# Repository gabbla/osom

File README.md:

# **Open speedomenter** **WIP**

**OSOM** (read as _ˈôsəm_) is the acronym of Open Speedometer.

## Architecture
The new architecture is the following:

Clinet <==BLE==> Master <==2.4GHz==> Slave

where:
- Master: CC2541 <==UART==> PIC <==SPI==> nRF24L01+
- Slave:  PIC <==SPI==> nRF24L01+

The client is a device that must be compatible with BLE (Bluetooth 4.x).

The CC2541 (aka NP, aka Network Processor) will run a standard firmware that is in charge of providing a bluetooth connection to the PIC.

Master and Slave will exchange messages over a custom, light-weight, protocol.

## Specifications

- Microcontroller: PIC32MX274F256D @72MHz (TODO verify)
- Communication:
	- Bluetooth (master only): HM10 Bluetooth 4.2 Low Energy
	- Wireless: nRF24L01+ @2.4GHz
- Power: 
	- LiPo 1s Battery, 1200/2000 mAh (not choosen yet)
	- 5V provided by micro USB, 500 mA MAX
- Sensor: custom made 650nm modulated laser sensor 
- Laser source: Red diode laser, 650nm @5mW

## PIC PIN assignment

### Bluetooth (master only)

PIN|I/O|PPS|Function|Note
--|--|--|--|--|
6|IN|RPB2|U1RX|PIC <== NP
7|OUT|RPB3|U1TX|PIC ==> NP

### nRF24L01+

PIN|I/O|PPS|Function|Note
--|--|--|--|--|
21|IN|RPB10|INT1|Interrupt generated by nRF24L01+
22|OUT|RPB11|SDO2|
23|OUT|-|CS|RB12
24|IN|RPB13|SDI2|
25|OUT|-|CE|RB14
26|OUT|RPB15|SCK2|

### Debug

PIN|I/O|PPS|Function|Note
--|--|--|--|--|
4|OUT|RPB0|U2TX|PIC ==> PC
5|IN|RPB1|U2RX|PIC <== PC

USB will be available too, with at least a _comunication device class_ (CDC) enumeration. 

### Sensing

PIN|I/O|PPS|Function|Note
--|--|--|--|--|
16|IN|-|INT0|Left IN Interrupt
11|IN|RPB4|INT4|Right IN Interrupt

### Battery Charger

New PIC analisys required

### LEDs

Analisys required. 

**Note**
1. Master only: an extra LED from CC2541 indicates the BT connection status.
2. From the battery charger an extra LED indicates che charging status.

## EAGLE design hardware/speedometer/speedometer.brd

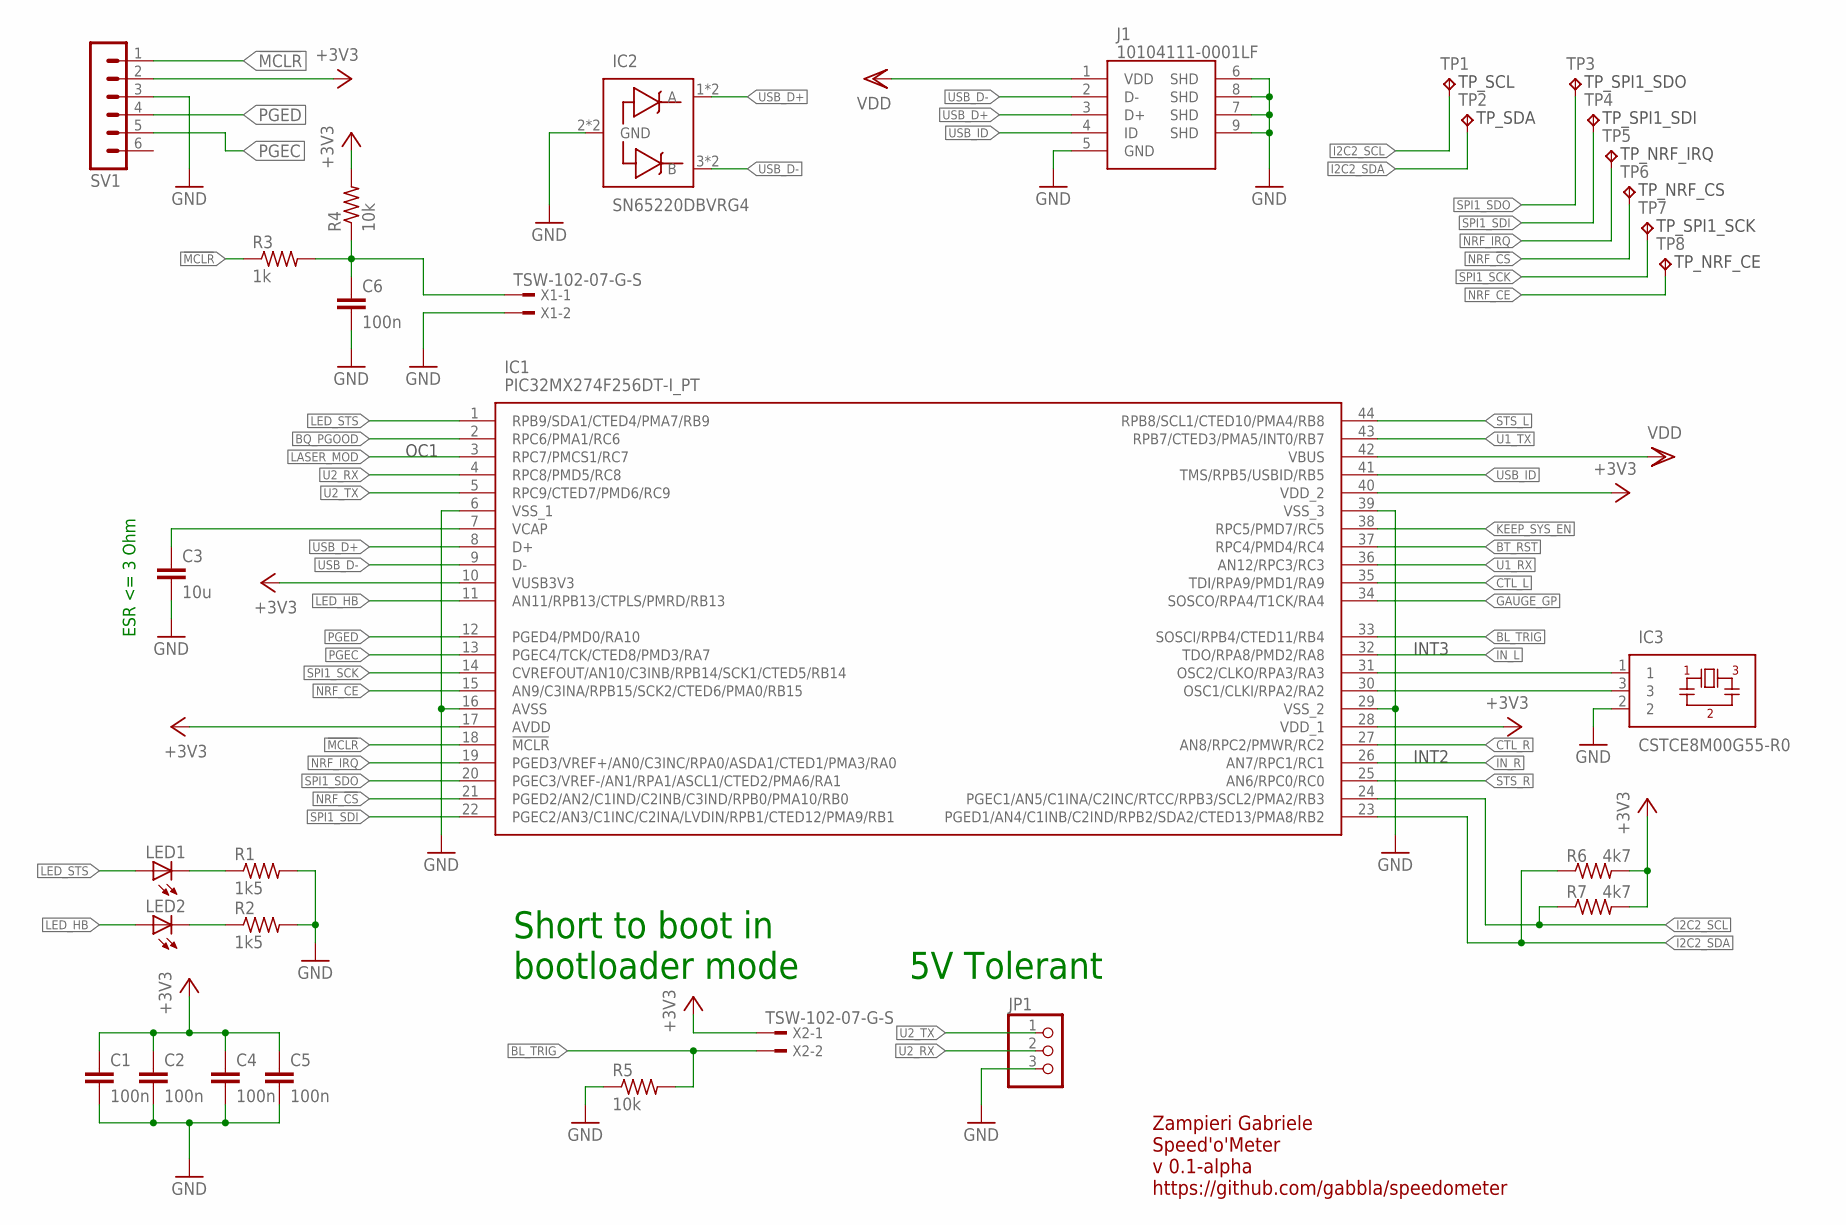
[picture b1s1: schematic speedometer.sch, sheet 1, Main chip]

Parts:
C1, C2, C4, C5, C6: 100n; C0603K
C3: 10u; C0805K
IC1: PIC32MX274F256DT-I_PT; QFP80P1200X1200X120-44N
IC2: SN65220DBVRG4; SOT95P280X145-6N
IC3: CSTCE8M00G55-R0; CSTCE_G
J1: 10104111-0001LF; MICRO_USB_A/B_TYPE_RECEPTACLE
JP1: PINHD-1X3; 1X03
LED1: LED3MM
LED2: LEDCHIPLED_0805; CHIPLED_0805
R1, R2: 1k5; R0603
R3: 1k; R0603
R4, R5: 10k; R0603
R6, R7: 4k7; R0603
SV1: MA06-1
TP1, TP2, TP3, TP4, TP5, TP6, TP7, TP8: TPB1,27; B1,27
X1, X2: TSW-102-07-G-S; TSW-102-XX-G-S

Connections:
!MCLR: IC1.18 (!MCLR), R3.1, SV1.1
+3V3: C1.1, C2.1, C4.1, C5.1, IC1.10 (VUSB3V3), IC1.17 (AVDD), IC1.28 (VDD_1), IC1.40 (VDD_2), R4.2, R6.2, R7.2, SV1.2, X2.1; also elsewhere on the board
BL_TRIG: IC1.33 (SOSCI/RPB4/CTED11/RB4), R5.2, X2.2
BQ_PGOOD: IC1.2 (RPC6/PMA1/RC6); also elsewhere on the board
BT_RST: IC1.37 (RPC4/PMD4/RC4); also elsewhere on the board
CTL_L: IC1.35 (TDI/RPA9/PMD1/RA9); also elsewhere on the board
CTL_R: IC1.27 (AN8/RPC2/PMWR/RC2); also elsewhere on the board
GAUGE_GP: IC1.34 (SOSCO/RPA4/T1CK/RA4); also elsewhere on the board
GND: C1.2, C2.2, C3.2, C4.2, C5.2, C6.2, IC1.6 (VSS_1), IC1.16 (AVSS), IC1.29 (VSS_2), IC1.39 (VSS_3), IC2.2 (GND), IC2.5 (GND), IC3.2, J1.5 (GND), J1.6 (SHD), J1.7 (SHD), J1.8 (SHD), J1.9 (SHD), JP1.3, R1.2, R2.2, R5.1, SV1.3, X1.2; also elsewhere on the board
I2C2_SCL: IC1.24 (PGEC1/AN5/C1INA/C2INC/RTCC/RPB3/SCL2/PM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), R7.1, TP1.TP; also elsewhere on the board
I2C2_SDA: IC1.23 (PGED1/AN4/C1INB/C2IND/RPB2/SDA2/CTED13/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), R6.1, TP2.TP; also elsewhere on the board
IN_L: IC1.32 (TDO/RPA8/PMD2/RA8); also elsewhere on the board
IN_R: IC1.26 (AN7/RPC1/RC1); also elsewhere on the board
KEEP_SYS_EN: IC1.38 (RPC5/PMD7/RC5); also elsewhere on the board
LASER_MOD: IC1.3 (RPC7/PMCS1/RC7); also elsewhere on the board
LED_HB: IC1.11 (AN11/RPB13/CTPLS/PMRD/RB13), LED2.A
LED_STS: IC1.1 (RPB9/SDA1/CTED4/PMA7/RB9), LED1.A
unnamed: LED1.K (C), R1.1
unnamed: IC1.31 (OSC2/CLKO/RPA3/RA3), IC3.1
unnamed: IC1.30 (OSC1/CLKI/RPA2/RA2), IC3.3
unnamed: C3.1, IC1.7 (VCAP)
unnamed: LED2.C, R2.1
unnamed: C6.1, R3.2, R4.1, X1.1
NRF_!CS: IC1.21 (PGED2/AN2/C1IND/C2INB/C3IND/RPB0/PMA10/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), TP6.TP; also elsewhere on the board
NRF_CE: IC1.15 (AN9/C3INA/RPB15/SCK2/CTED6/PMA0/RB15), TP8.TP; also elsewhere on the board
NRF_IRQ: IC1.19 (PGED3/VREF+/AN0/C3INC/RPA0/ASDA1/CTED1/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), TP5.TP; also elsewhere on the board
PGEC: IC1.13 (PGEC4/TCK/CTED8/PMD3/RA7), SV1.5
PGED: IC1.12 (PGED4/PMD0/RA10), SV1.4
SPI1_SCK: IC1.14 (CVREFOUT/AN10/C3INB/RPB14/SCK1/CTED5/RB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), TP7.TP; also elsewhere on the board
SPI1_SDI: IC1.22 (PGEC2/AN3/C1INC/C2INA/LVDIN/RPB1/CTED12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), TP4.TP; also elsewhere on the board
SPI1_SDO: IC1.20 (PGEC3/VREF-/AN1/RPA1/ASCL1/CTED2/PMA6/R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), TP3.TP; also elsewhere on the board
STS_L: IC1.44 (RPB8/SCL1/CTED10/PMA4/RB8); also elsewhere on the board
STS_R: IC1.25 (AN6/RPC0/RC0); also elsewhere on the board
U1_RX: IC1.36 (AN12/RPC3/RC3); also elsewhere on the board
U1_TX: IC1.43 (RPB7/CTED3/PMA5/INT0/RB7); also elsewhere on the board
U2_RX: IC1.4 (RPC8/PMD5/RC8), JP1.2
U2_TX: IC1.5 (RPC9/CTED7/PMD6/RC9), JP1.1
USB_D+: IC1.8 (D+), IC2.1 (A), IC2.6 (A), J1.3 (D+)
USB_D-: IC1.9 (D-), IC2.3 (B), IC2.4 (B), J1.2 (D-)
USB_ID: IC1.41 (TMS/RPB5/USBID/RB5), J1.4 (ID)
VDD: IC1.42 (VBUS), J1.1 (VDD); also elsewhere on the board

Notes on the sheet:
Zampieri Gabriele Speed'o'Meter v 0.1-alpha https://github.com/gabbla/speedometer
ESR <= 3 Ohm
5V Tolerant
Short to boot in bootloader mode
OC1
INT2
INT3

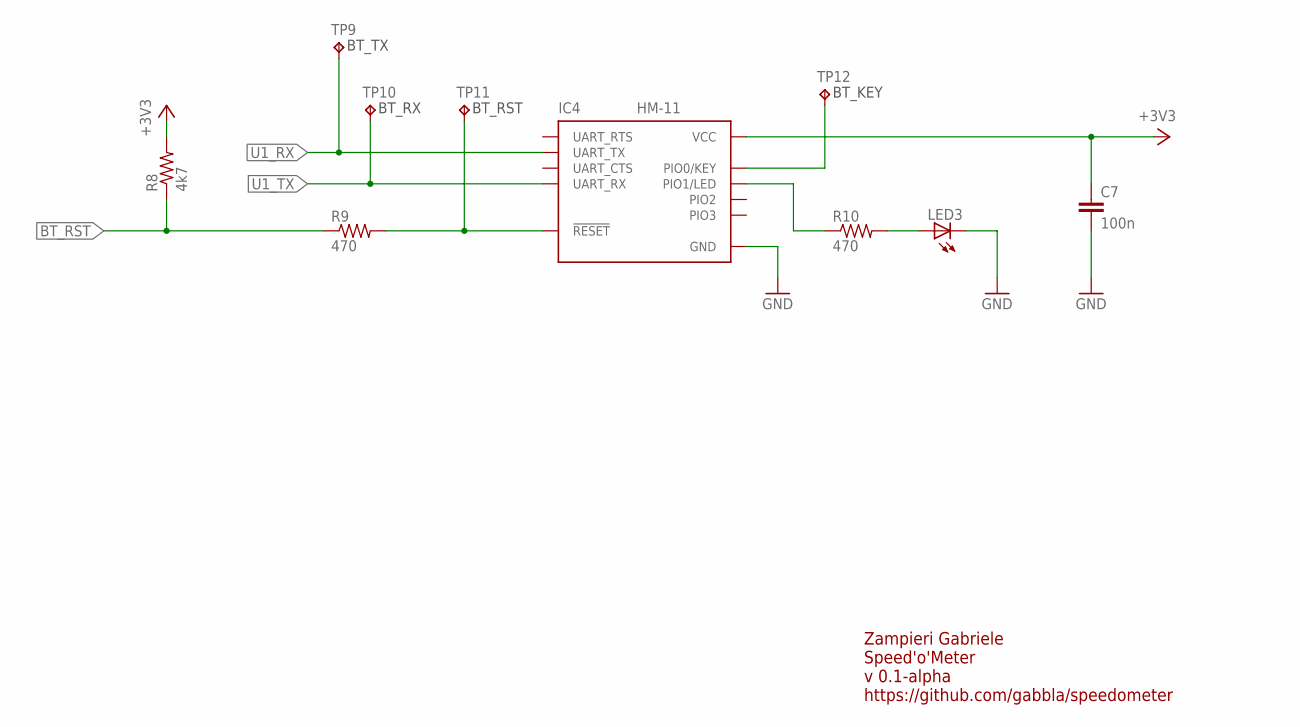
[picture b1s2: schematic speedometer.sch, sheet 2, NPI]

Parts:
C7: 100n; C0603K
IC4: HM-11
LED3: LED3MM
R8: 4k7; R0603
R9, R10: 470; R0603
TP9, TP10, TP11, TP12: TPB1,27; B1,27

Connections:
+3V3: C7.1, IC4.VCC, R8.2; also elsewhere on the board
BT_RST: R8.1, R9.1; also elsewhere on the board
GND: C7.2, IC4.GND, LED3.K (C); also elsewhere on the board
unnamed: IC4.RESETB (!RESET), R9.2, TP11.TP
unnamed: IC4.PIO0 (PIO0/KEY), TP12.TP
unnamed: IC4.PIO1 (PIO1/LED), R10.1
unnamed: LED3.A, R10.2
U1_RX: IC4.UART_TX, TP9.TP; also elsewhere on the board
U1_TX: IC4.UART_RX, TP10.TP; also elsewhere on the board

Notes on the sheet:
Zampieri Gabriele Speed'o'Meter v 0.1-alpha https://github.com/gabbla/speedometer

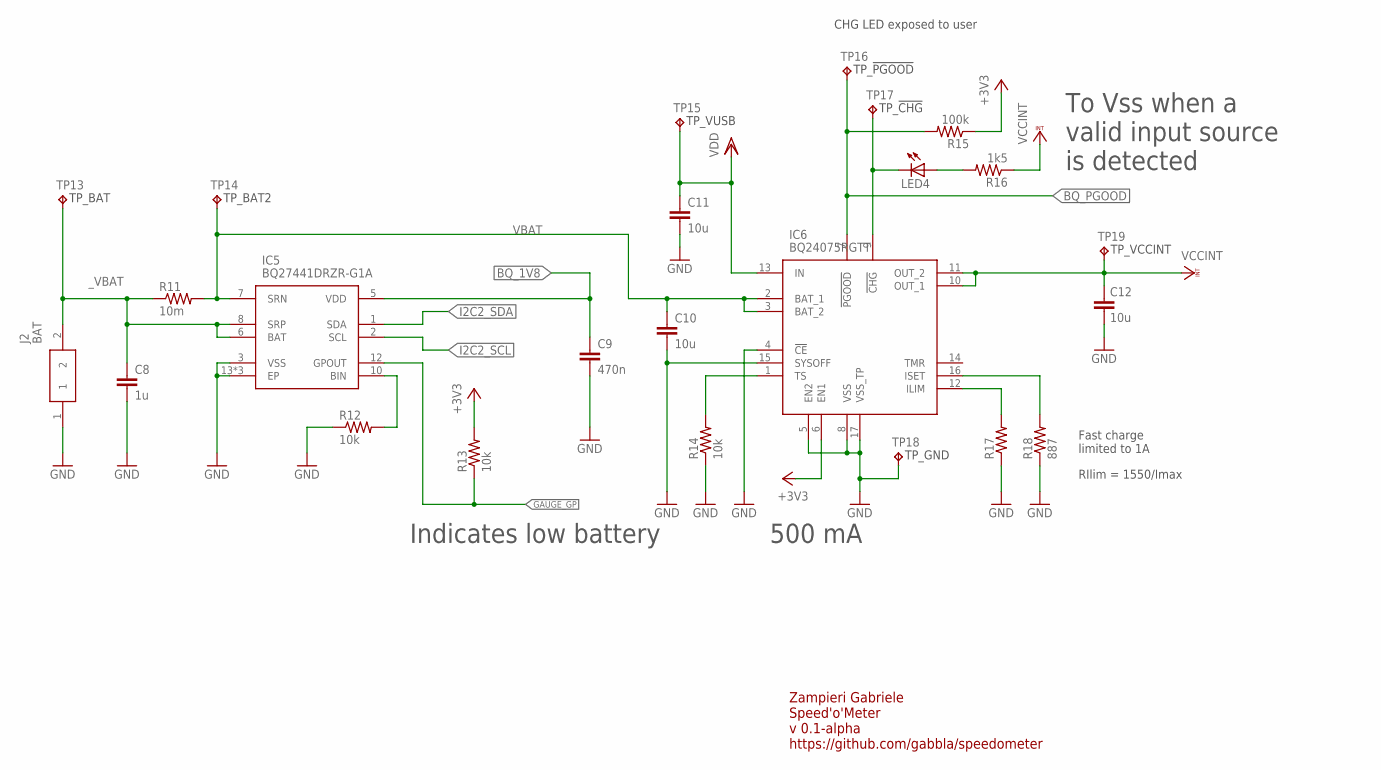
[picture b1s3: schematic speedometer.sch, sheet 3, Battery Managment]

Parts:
C8: 1u; C0603K
C9: 470n; C0603K
C10, C11, C12: 10u; C0805K
IC5: BQ27441DRZR-G1A; BQ27441DRZRG1A
IC6: BQ24075RGTT; QFN50P300X300X80-17N
J2: BAT; B2B-PH-SM4-TB
LED4: LED3MM
R11: 10m; R2512
R12, R13, R14: 10k; R0603
R15: 100k; R0603
R16: 1k5; R0603
R17: R-US_R0603; R0603
R18: 887; R0603
TP13, TP14, TP15, TP16, TP17, TP18, TP19: TPB1,27; B1,27

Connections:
!BAT_CHG: IC6.9 (!CHG), LED4.K (C), TP17.TP
+3V3: IC6.6 (EN1), R13.2, R15.1; also elsewhere on the board
BQ_1V8: C9.1, IC5.5 (VDD)
BQ_PGOOD: IC6.7 (!PGOOD), R15.2, TP16.TP; also elsewhere on the board
GAUGE_GP: IC5.12 (GPOUT), R13.1; also elsewhere on the board
GND: C8.2, C9.2, C10.2, C11.2, C12.2, IC5.3 (VSS), IC5.13 (EP), IC5.14 (EP), IC5.15 (EP), IC6.4 (!CE), IC6.5 (EN2), IC6.8 (VSS), IC6.15 (SYSOFF), IC6.17 (VSS_TP), J2.1, R12.1, R14.1, R17.1, R18.1, TP18.TP; also elsewhere on the board
I2C2_SCL: IC5.2 (SCL); also elsewhere on the board
I2C2_SDA: IC5.1 (SDA); also elsewhere on the board
unnamed: IC6.1 (TS), R14.2
unnamed: IC6.12 (ILIM), R17.2
unnamed: IC6.16 (ISET), R18.2
unnamed: LED4.A, R16.2
unnamed: IC5.10 (BIN), R12.2
VBAT: C10.1, IC5.7 (SRN), IC6.2 (BAT_1), IC6.3 (BAT_2), R11.2, TP14.TP
VCCINT: C12.1, IC6.10 (OUT_1), IC6.11 (OUT_2), R16.1, TP19.TP; also elsewhere on the board
VDD: C11.1, IC6.13 (IN), TP15.TP; also elsewhere on the board
_VBAT: C8.1, IC5.6 (BAT), IC5.8 (SRP), J2.2, R11.1, TP13.TP

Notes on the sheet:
CHG LED exposed to user
Zampieri Gabriele Speed'o'Meter v 0.1-alpha https://github.com/gabbla/speedometer
500 mA
To Vss when a valid input source is detected
Indicates low battery
Fast charge limited to 1A
RIlim = 1550/Imax

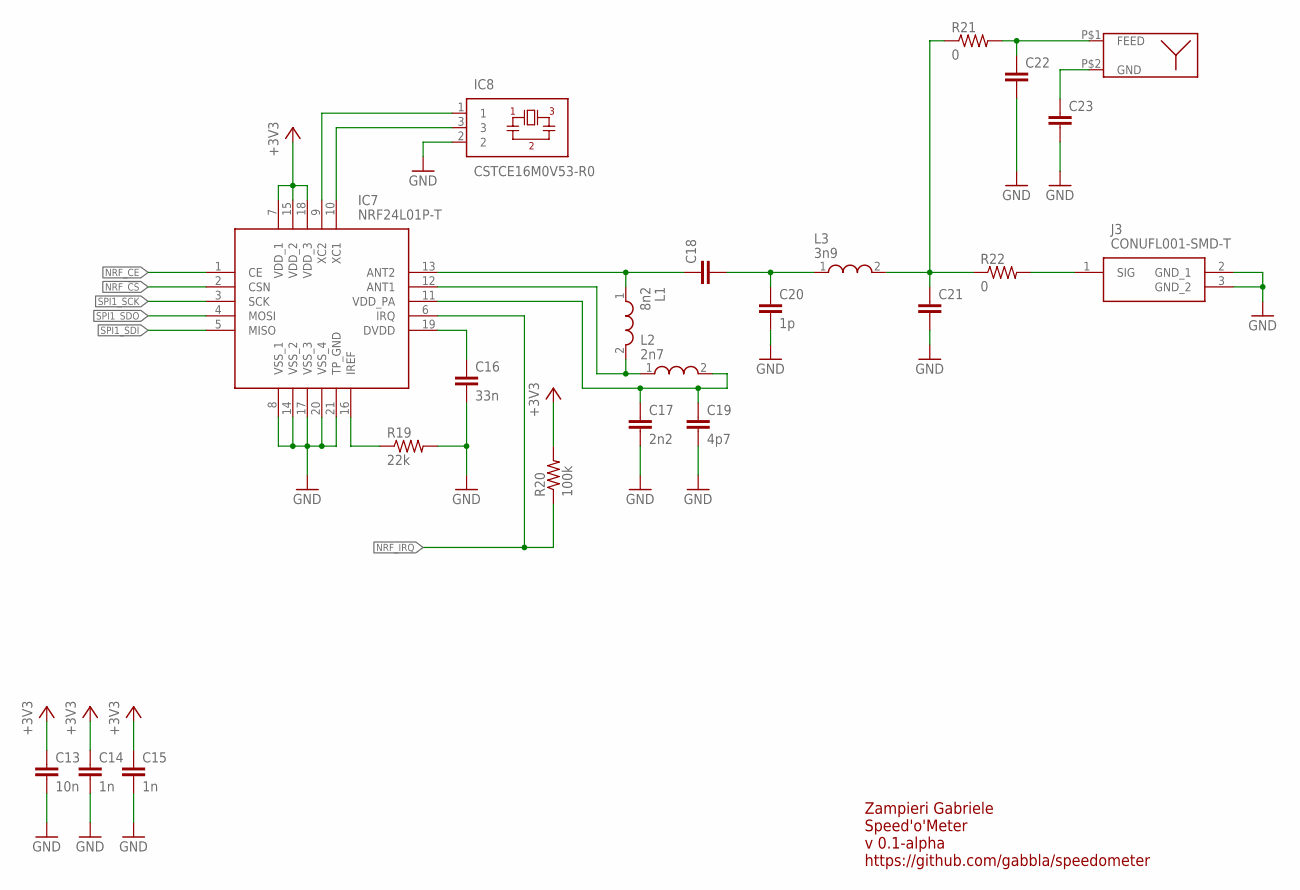
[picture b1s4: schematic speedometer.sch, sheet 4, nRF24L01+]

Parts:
ANT1: M310210
C13: 10n; C0603K
C14, C15: 1n; C0603K
C16: 33n; C0402K
C17: 2n2; C0402K
C18, C21, C22, C23: C-EUC0402K; C0402K
C19: 4p7; C0402K
C20: 1p; C0402K
IC7: NRF24L01P-T; QFN50P400X400X95-21N
IC8: CSTCE16M0V53-R0; CSTCE_G
J3: CONUFL001-SMD-T; CONUFL001-SMD
L1: 8n2; C0402K
L2: 2n7; C0402K
L3: 3n9; C0402K
R19: 22k; R0603
R20: 100k; R0603
R21, R22: 0; R0402

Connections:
+3V3: C13.1, C14.1, C15.1, IC7.7 (VDD_1), IC7.15 (VDD_2), IC7.18 (VDD_3), R20.2; also elsewhere on the board
GND: C13.2, C14.2, C15.2, C16.2, C17.2, C19.2, C20.2, C21.2, C22.2, C23.2, IC7.8 (VSS_1), IC7.14 (VSS_2), IC7.17 (VSS_3), IC7.20 (VSS_4), IC7.21 (TP_GND), IC8.2, J3.2 (GND_1), J3.3 (GND_2), R19.2; also elsewhere on the board
unnamed: C18.2, C20.1, L3.1
unnamed: C21.1, L3.2, R21.1, R22.1
unnamed: IC7.9 (XC2), IC8.1
unnamed: J3.1 (SIG), R22.2
unnamed: IC7.16 (IREF), R19.1
unnamed: C16.1, IC7.19 (DVDD)
unnamed: IC7.10 (XC1), IC8.3
unnamed: C18.1, IC7.13 (ANT2), L1.1
unnamed: IC7.12 (ANT1), L1.2, L2.1
unnamed: C17.1, C19.1, IC7.11 (VDD_PA), L2.2
unnamed: ANT1.P$2 (GND), C23.1
unnamed: ANT1.P$1 (FEED), C22.1, R21.2
NRF_!CS: IC7.2 (CSN); also elsewhere on the board
NRF_CE: IC7.1 (CE); also elsewhere on the board
NRF_IRQ: IC7.6 (IRQ), R20.1; also elsewhere on the board
SPI1_SCK: IC7.3 (SCK); also elsewhere on the board
SPI1_SDI: IC7.5 (MISO); also elsewhere on the board
SPI1_SDO: IC7.4 (MOSI); also elsewhere on the board

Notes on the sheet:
Zampieri Gabriele Speed'o'Meter v 0.1-alpha https://github.com/gabbla/speedometer

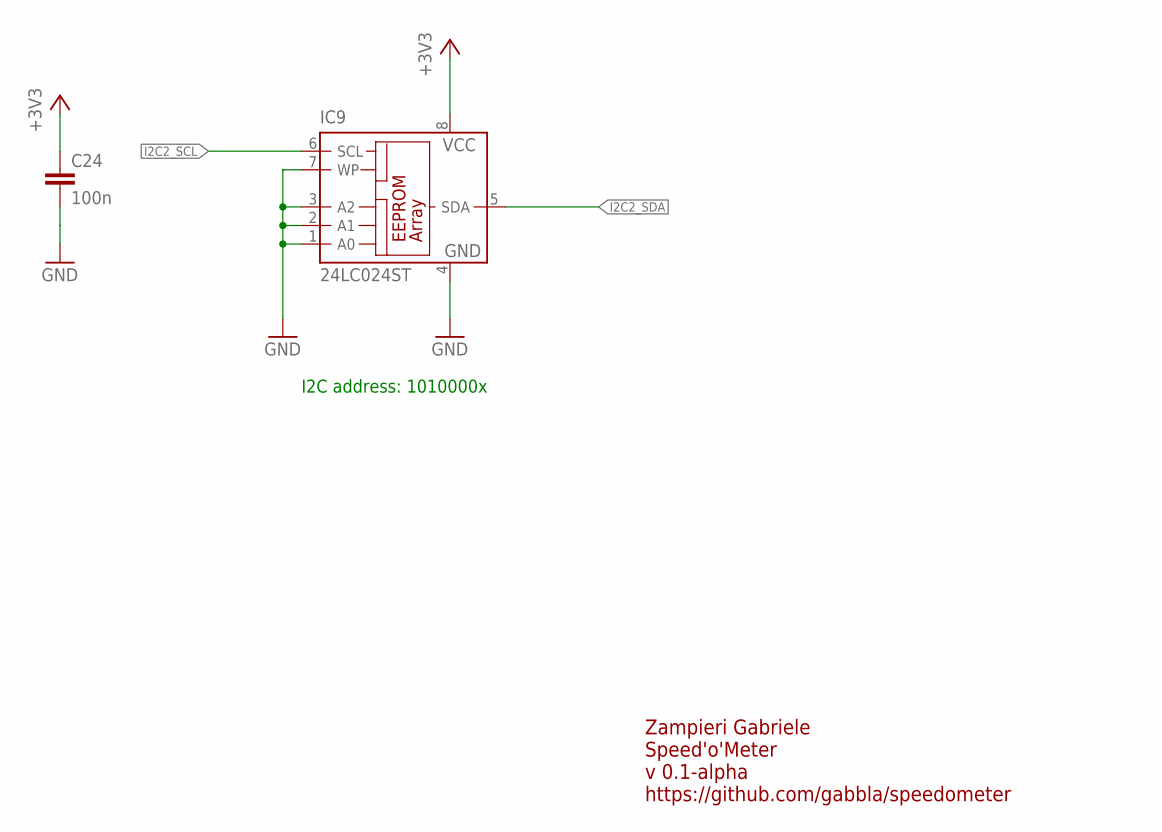
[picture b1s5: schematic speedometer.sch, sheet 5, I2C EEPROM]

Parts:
C24: 100n; C0603K
IC9: 24LC024ST; TSSOP8

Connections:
+3V3: C24.1, IC9.8 (VCC); also elsewhere on the board
GND: C24.2, IC9.1 (A0), IC9.2 (A1), IC9.3 (A2), IC9.4 (GND), IC9.7 (WP); also elsewhere on the board
I2C2_SCL: IC9.6 (SCL); also elsewhere on the board
I2C2_SDA: IC9.5 (SDA); also elsewhere on the board

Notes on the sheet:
I2C address: 1010000x
Zampieri Gabriele Speed'o'Meter v 0.1-alpha https://github.com/gabbla/speedometer

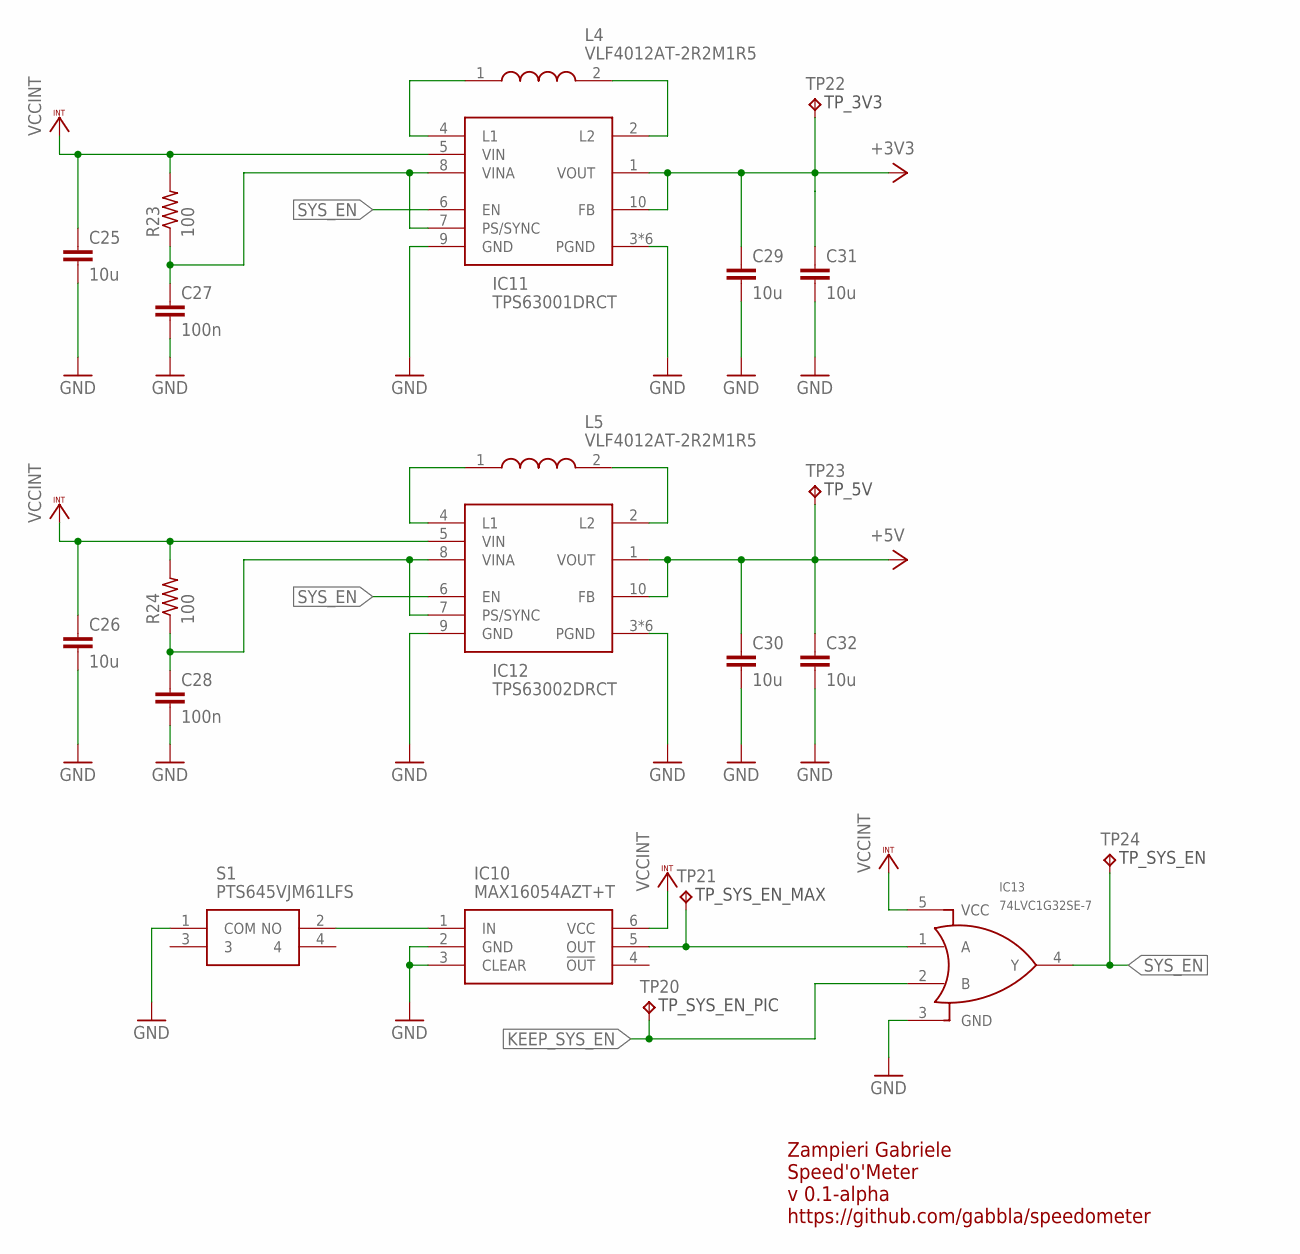
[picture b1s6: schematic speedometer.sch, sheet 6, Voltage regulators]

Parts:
C25, C26, C29, C30, C31, C32: 10u; C0805K
C27, C28: 100n; C0603K
IC10: MAX16054AZT+T; SOT95P275X110-6N
IC11: TPS63001DRCT; SON50P300X300X100-11N
IC12: TPS63002DRCT; SON50P300X300X100-11N
IC13: 74LVC1G32SE-7; SOT353
L4, L5: VLF4012AT-2R2M1R5; LPS3015
R23, R24: 100; R0603
S1: PTS645VJM61LFS
TP20, TP21, TP22, TP23, TP24: TPB1,27; B1,27

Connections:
+3V3: C29.1, C31.1, IC11.1 (VOUT), IC11.10 (FB), TP22.TP; also elsewhere on the board
+5V: C30.1, C32.1, IC12.1 (VOUT), IC12.10 (FB), TP23.TP; also elsewhere on the board
GND: C25.2, C26.2, C27.2, C28.2, C29.2, C30.2, C31.2, C32.2, IC10.2 (GND), IC10.3 (CLEAR), IC11.3 (PGND), IC11.9 (GND), IC11.11 (PGND), IC11.EP1 (PGND), IC11.EP2 (PGND), IC11.EP3 (PGND), IC11.EP4 (PGND), IC12.3 (PGND), IC12.9 (GND), IC12.11 (PGND), IC12.EP1 (PGND), IC12.EP2 (PGND), IC12.EP3 (PGND), IC12.EP4 (PGND), IC13.3 (GND), S1.1 (COM); also elsewhere on the board
KEEP_SYS_EN: IC13.2 (B), TP20.TP; also elsewhere on the board
MAX_SYS_ON: IC10.5 (OUT), IC13.1 (A), TP21.TP
unnamed: IC11.4 (L1), L4.1
unnamed: IC11.2 (L2), L4.2
unnamed: IC10.1 (IN), S1.2 (NO)
unnamed: IC12.4 (L1), L5.1
unnamed: C27.1, IC11.7 (PS/SYNC), IC11.8 (VINA), R23.1
unnamed: IC12.2 (L2), L5.2
unnamed: C28.1, IC12.7 (PS/SYNC), IC12.8 (VINA), R24.1
SYS_EN: IC11.6 (EN), IC12.6 (EN), IC13.4 (Y), TP24.TP
VCCINT: C25.1, C26.1, IC10.6 (VCC), IC11.5 (VIN), IC12.5 (VIN), IC13.5 (VCC), R23.2, R24.2; also elsewhere on the board

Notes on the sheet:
Zampieri Gabriele Speed'o'Meter v 0.1-alpha https://github.com/gabbla/speedometer

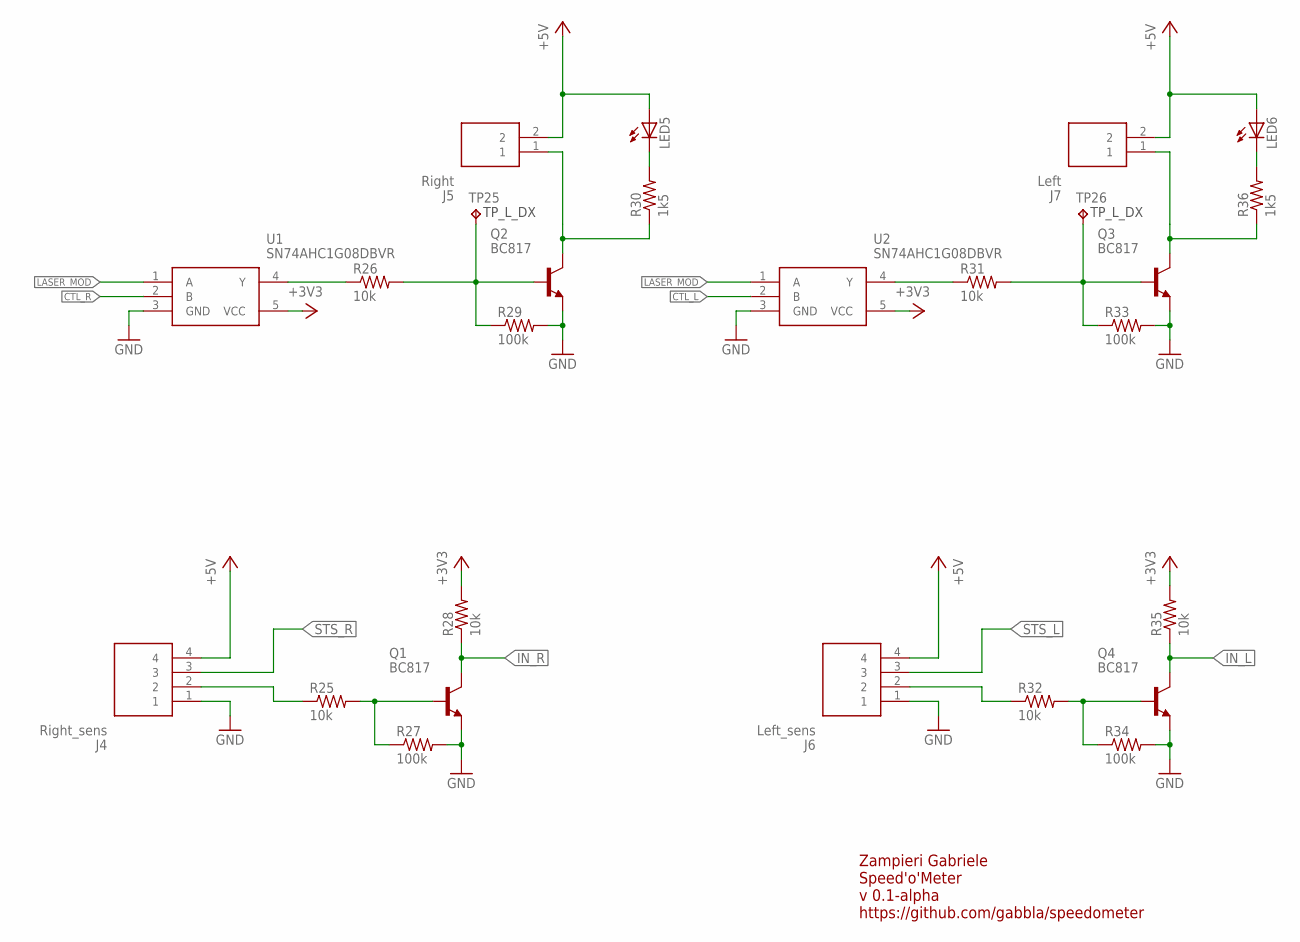
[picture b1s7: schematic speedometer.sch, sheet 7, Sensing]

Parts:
J4: Right_sens; SHDR4W64P0X250_1X4_1240X575X70
J5: Right; SHDR2W64P0X250_1X2_740X575X700
J6: Left_sens; SHDR4W64P0X250_1X4_1240X575X70
J7: Left; SHDR2W64P0X250_1X2_740X575X700
LED5, LED6: LEDCHIPLED_1206; CHIPLED_1206
Q1, Q2, Q3, Q4: BC817; SOT23-BEC
R25, R26, R28, R31, R32, R35: 10k; R0603
R27, R29, R33, R34: 100k; R0603
R30, R36: 1k5; R0603
TP25, TP26: TPB1,27; B1,27
U1, U2: SN74AHC1G08DBVR; SOT95P280X145-5N

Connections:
+3V3: R28.2, R35.2, U1.5 (VCC), U2.5 (VCC); also elsewhere on the board
+5V: J4.4, J5.2, J6.4, J7.2, LED5.A, LED6.A; also elsewhere on the board
CTL_L: U2.2 (B); also elsewhere on the board
CTL_R: U1.2 (B); also elsewhere on the board
GND: J4.1, J6.1, Q1.E, Q2.E, Q3.E, Q4.E, R27.2, R29.2, R33.2, R34.2, U1.3 (GND), U2.3 (GND); also elsewhere on the board
IN_L: Q4.C, R35.1; also elsewhere on the board
IN_R: Q1.C, R28.1; also elsewhere on the board
LASER_MOD: U1.1 (A), U2.1 (A); also elsewhere on the board
unnamed: J7.1, Q3.C, R36.1
unnamed: Q4.B, R32.2, R34.1
unnamed: Q3.B, R31.2, R33.1, TP26.TP
unnamed: LED6.C, R36.2
unnamed: R31.1, U2.4 (Y)
unnamed: Q1.B, R25.2, R27.1
unnamed: J4.2, R25.1
unnamed: J6.2, R32.1
unnamed: J5.1, Q2.C, R30.1
unnamed: Q2.B, R26.2, R29.1, TP25.TP
unnamed: LED5.C, R30.2
unnamed: R26.1, U1.4 (Y)
STS_L: J6.3; also elsewhere on the board
STS_R: J4.3; also elsewhere on the board

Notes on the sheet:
Zampieri Gabriele Speed'o'Meter v 0.1-alpha https://github.com/gabbla/speedometer

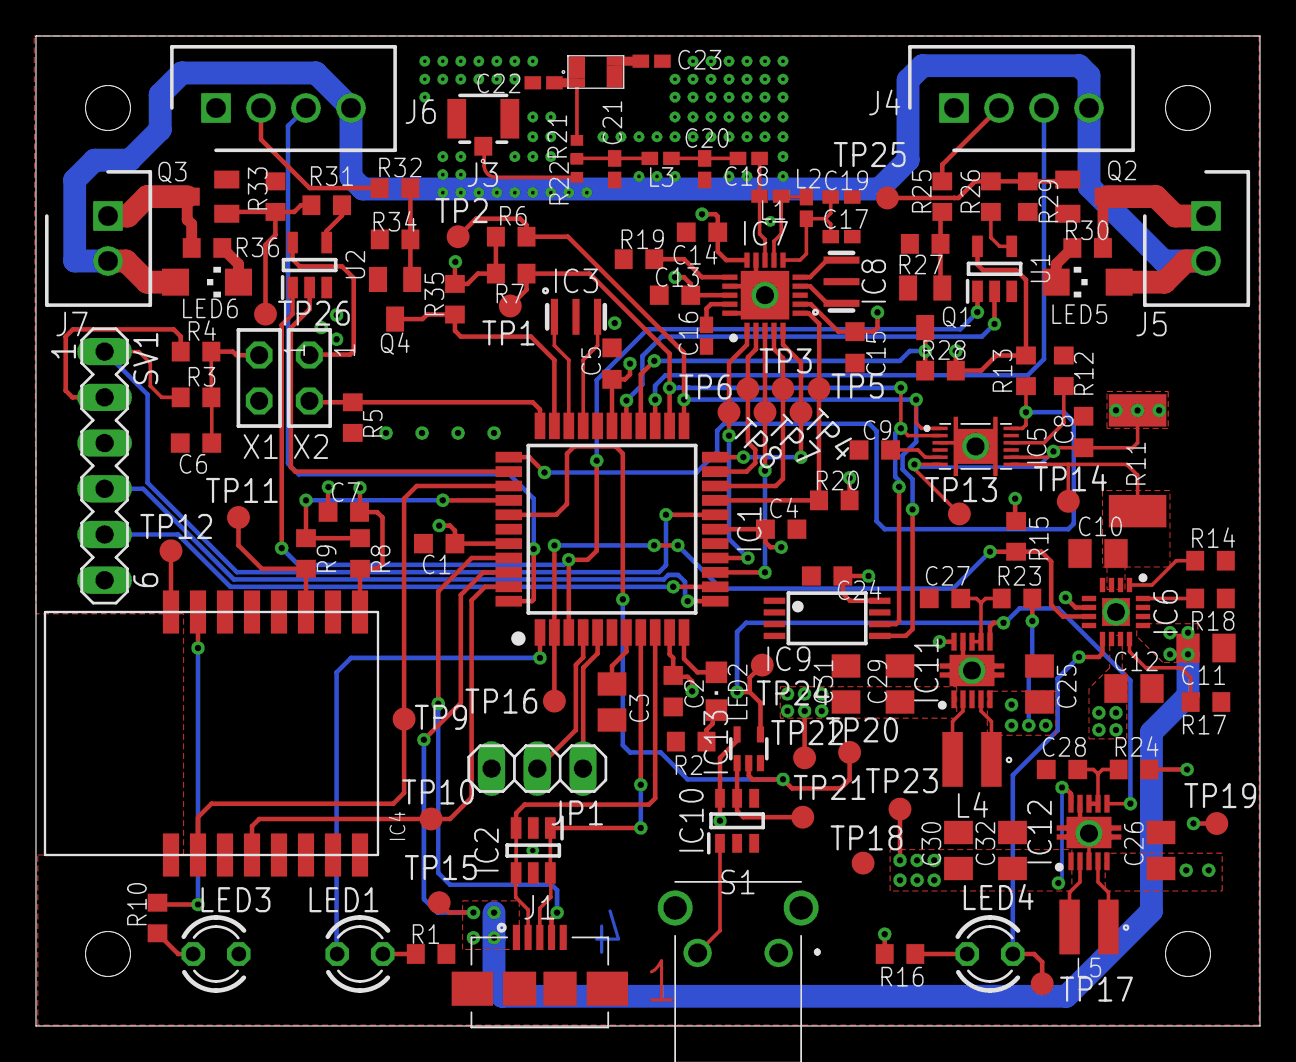
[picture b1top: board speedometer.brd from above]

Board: 4 copper layers, 68.0 x 55.0 mm, 137 parts (1 on the bottom side), 89 nets.

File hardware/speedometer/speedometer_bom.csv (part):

"Part";"Value";"Device";"Package";"Description";"ALLIED_NUMBER";"ARROW_PART_NUMBER";"ARROW_PRICE-STOCK";"ARROW_PRICE/STOCK";"DESCRIPTION";"HEIGHT";"MANUFACTURER_NAME";"MANUFACTURER_PART_NUMBER";"MF";"MPN";"OC_FARNELL";"OC_NEWARK";"RS";"RS_PART_NUMBER";"RS_PRICE-STOCK";"RS_PRICE/STOCK";"SPICEPREFIX";"TP_SIGNAL_NAME";
"ANT1";"M310210";"M310210";"M310210";"";"";"";"";"";"";"";"";"";"";"";"";"";"";"";"";"";"";"";
"C1";"100n";"C-EUC0603K";"C0603K";"CAPACITOR, European symbol";"";"";"";"";"";"";"";"";"";"";"";"";"";"";"";"";"C";"";
"C2";"100n";"C-EUC0603K";"C0603K";"CAPACITOR, European symbol";"";"";"";"";"";"";"";"";"";"";"";"";"";"";"";"";"C";"";
"C3";"10u";"C-EUC0805K";"C0805K";"CAPACITOR, European symbol";"";"";"";"";"";"";"";"";"";"";"";"";"";"";"";"";"C";"";
"C4";"100n";"C-EUC0603K";"C0603K";"CAPACITOR, European symbol";"";"";"";"";"";"";"";"";"";"";"";"";"";"";"";"";"C";"";
"C5";"100n";"C-EUC0603K";"C0603K";"CAPACITOR, European symbol";"";"";"";"";"";"";"";"";"";"";"";"";"";"";"";"";"C";"";
"C6";"100n";"C-EUC0603K";"C0603K";"CAPACITOR, European symbol";"";"";"";"";"";"";"";"";"";"";"";"";"";"";"";"";"C";"";
"C7";"100n";"C-EUC0603K";"C0603K";"CAPACITOR, European symbol";"";"";"";"";"";"";"";"";"";"";"";"";"";"";"";"";"C";"";
"C8";"1u";"C-EUC0603K";"C0603K";"CAPACITOR, European symbol";"";"";"";"";"";"";"";"";"";"";"";"";"";"";"";"";"C";"";
"C9";"470n";"C-EUC0603K";"C0603K";"CAPACITOR, European symbol";"";"";"";"";"";"";"";"";"";"";"";"";"";"";"";"";"C";"";
"C10";"10u";"C-EUC0805K";"C0805K";"CAPACITOR, European symbol";"";"";"";"";"";"";"";"";"";"";"";"";"";"";"";"";"C";"";
"C11";"10u";"C-EUC0805K";"C0805K";"CAPACITOR, European symbol";"";"";"";"";"";"";"";"";"";"";"";"";"";"";"";"";"C";"";
"C12";"10u";"C-EUC0805K";"C0805K";"CAPACITOR, European symbol";"";"";"";"";"";"";"";"";"";"";"";"";"";"";"";"";"C";"";
"C13";"10n";"C-EUC0603K";"C0603K";"CAPACITOR, European symbol";"";"";"";"";"";"";"";"";"";"";"";"";"";"";"";"";"C";"";
"C14";"1n";"C-EUC0603K";"C0603K";"CAPACITOR, European symbol";"";"";"";"";"";"";"";"";"";"";"";"";"";"";"";"";"C";"";
"C15";"1n";"C-EUC0603K";"C0603K";"CAPACITOR, European symbol";"";"";"";"";"";"";"";"";"";"";"";"";"";"";"";"";"C";"";
"C16";"33n";"C-EUC0402K";"C0402K";"CAPACITOR, European symbol";"";"";"";"";"";"";"";"";"";"";"";"";"";"";"";"";"C";"";
"C17";"2n2";"C-EUC0402K";"C0402K";"CAPACITOR, European symbol";"";"";"";"";"";"";"";"";"";"";"";"";"";"";"";"";"C";"";
"C18";"";"C-EUC0402K";"C0402K";"CAPACITOR, European symbol";"";"";"";"";"";"";"";"";"";"";"";"";"";"";"";"";"C";"";
"C19";"4p7";"C-EUC0402K";"C0402K";"CAPACITOR, European symbol";"";"";"";"";"";"";"";"";"";"";"";"";"";"";"";"";"C";"";
"C20";"1p";"C-EUC0402K";"C0402K";"CAPACITOR, European symbol";"";"";"";"";"";"";"";"";"";"";"";"";"";"";"";"";"C";"";
"C21";"";"C-EUC0402K";"C0402K";"CAPACITOR, European symbol";"";"";"";"";"";"";"";"";"";"";"";"";"";"";"";"";"C";"";
"C22";"";"C-EUC0402K";"C0402K";"CAPACITOR, European symbol";"";"";"";"";"";"";"";"";"";"";"";"";"";"";"";"";"C";"";
"C23";"";"C-EUC0402K";"C0402K";"CAPACITOR, European symbol";"";"";"";"";"";"";"";"";"";"";"";"";"";"";"";"";"C";"";
"C24";"100n";"C-EUC0603K";"C0603K";"CAPACITOR, European symbol";"";"";"";"";"";"";"";"";"";"";"";"";"";"";"";"";"C";"";
"C25";"10u";"C-EUC0805K";"C0805K";"CAPACITOR, European symbol";"";"";"";"";"";"";"";"";"";"";"";"";"";"";"";"";"C";"";
"C26";"10u";"C-EUC0805K";"C0805K";"CAPACITOR, European symbol";"";"";"";"";"";"";"";"";"";"";"";"";"";"";"";"";"C";"";
"C27";"100n";"C-EUC0603K";"C0603K";"CAPACITOR, European symbol";"";"";"";"";"";"";"";"";"";"";"";"";"";"";"";"";"C";"";
"C28";"100n";"C-EUC0603K";"C0603K";"CAPACITOR, European symbol";"";"";"";"";"";"";"";"";"";"";"";"";"";"";"";"";"C";"";
"C29";"10u";"C-EUC0805K";"C0805K";"CAPACITOR, European symbol";"";"";"";"";"";"";"";"";"";"";"";"";"";"";"";"";"C";"";
"C30";"10u";"C-EUC0805K";"C0805K";"CAPACITOR, European symbol";"";"";"";"";"";"";"";"";"";"";"";"";"";"";"";"";"C";"";
"C31";"10u";"C-EUC0805K";"C0805K";"CAPACITOR, European symbol";"";"";"";"";"";"";"";"";"";"";"";"";"";"";"";"";"C";"";
"C32";"10u";"C-EUC0805K";"C0805K";"CAPACITOR, European symbol";"";"";"";"";"";"";"";"";"";"";"";"";"";"";"";"";"C";"";
"IC1";"PIC32MX274F256DT-I_PT";"PIC32MX274F256DT-I_PT";"QFP80P1200X1200X120-44N";"32-bit Microcontrollers - MCU 256KB Flash, 64KB RAM, 10-Bit ADC, UART, SPI/I2S, I2C + VBATT Pin, USB";"";"PIC32MX274F256DT-I/PT";"";"";"32-bit Microcontrollers - MCU 256KB Flash, 64KB RAM, 10-Bit ADC, UART, SPI/I2S, I2C + VBATT Pin, USB";"1.2mm";"Microchip";"PIC32MX274F256DT-I/PT";"";"";"";"";"";"";"";"";"";"";
"IC2";"SN65220DBVRG4";"SN65220DBVRG4";"SOT95P280X145-6N";"ESD Suppressors / TVS Diodes Sngl Port Transient Suppressor";"";"SN65220DBVRG4";"";"https://www.arrow.com/en/products/sn65220dbvrg4/texas-instruments";"ESD Suppressors / TVS Diodes Sngl Port Transient Suppressor";"1.45mm";"Texas Instruments";"SN65220DBVRG4";"";"";"";"";"";"";"";"";"";"";
"IC3";"CSTCE8M00G55-R0";"CSTCE12M0G15L99-R0";"CSTCE_G";"CSTCE12M0G15L99-R0, Ceramic Resonator, 12MHz Shear 33pF, 3-Pin SMT, 3.2 x 1.3 x 0.7mm";"";"CSTCE12M0G15L99-R0";"";"https://www.arrow.com/en/products/cstce12m0g15l99-r0/murata-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";"CSTCE12M0G15L99-R0, Ceramic Resonator, 12MHz Shear 33pF, 3-Pin SMT, 3.2 x 1.3 x 0.7mm";"mm";"Murata Electronics";"CSTCE12M0G15L99-R0";"";"";"";"";"";"7926527P";"";"http://uk.rs-online.com/web/p/products/7926527P";"";"";
"IC4";"HM-11";"HM-11";"HM-11";"JNHuaMao HM-11 Bluetooth 4.0 Transceiver";"";"";"";"";"";"";"";"";"";"";"";"";"";"";"";"";"";"";
"IC5";"BQ27441DRZR-G1A";"BQ27441DRZR-G1A";"BQ27441DRZRG1A";"System-Side Impedance Track Battery Fuel (Gas) Gauge";"";"BQ27441DRZR-G1A";"https://www.arrow.com/en/products/bq27441drzr-g1a/texas-instruments";"";"System-Side Impedance Track Battery Fuel (Gas) Gauge";"mm";"Texas Instruments";"BQ27441DRZR-G1A";"";"";"";"";"";"";"";"";"";"";
"IC6";"BQ24075RGTT";"BQ24075RGTT";"QFN50P300X300X80-17N";"1.5A Li-Ion Charger, Power-Path VQFN16EP BQ24075RGTT, Battery Charge Controller, Lithium-Ion, 4500mA, 16-Pin QFN";"";"BQ24075RGTT";"";"https://www.arrow.com/en/products/bq24075rgtt/texas-instruments";"1.5A Li-Ion Charger, Power-Path VQFN16EP BQ24075RGTT, Battery Charge Controller, Lithium-Ion, 4500mA, 16-Pin QFN";"0.8mm";"Texas Instruments";"BQ24075RGTT";"";"";"";"";"";"8175815P";"";"http://uk.rs-online.com/web/p/products/8175815P";"";"";
"IC7";"NRF24L01P-T";"NRF24L01P-T";"QFN50P400X400X95-21N";"RF Transceiver IC 2.4GHz ISM Band QFN20 Nordic Semiconductor NRF24L01P-T, RF Transceiver 2400MHz to 2483.5MHz 1.9  3.6 V 20-Pin QFN";"";"nRF24L01P-T";"";"https://www.arrow.com/en/products/nrf24l01p-t/nordic-semiconductor";"RF Transceiver IC 2.4GHz ISM Band QFN20 Nordic Semiconductor NRF24L01P-T, RF Transceiver 2400MHz to 2483.5MHz 1.9  3.6 V 20-Pin QFN";"0.95mm";"Nordic Semiconductor";"nRF24L01P-T";"";"";"";"";"";"8855748P";"";"http://uk.rs-online.com/web/p/products/8855748P";"";"";
"IC8";"CSTCE16M0V53-R0";"CSTCE12M0G15L99-R0";"CSTCE_G";"CSTCE12M0G15L99-R0, Ceramic Resonator, 12MHz Shear 33pF, 3-Pin SMT, 3.2 x 1.3 x 0.7mm";"";"CSTCE12M0G15L99-R0";"";"https://www.arrow.com/en/products/cstce12m0g15l99-r0/murata-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";"CSTCE12M0G15L99-R0, Ceramic Resonator, 12MHz Shear 33pF, 3-Pin SMT, 3.2 x 1.3 x 0.7mm";"mm";"Murata Electronics";"CSTCE12M0G15L99-R0";"";"";"";"";"";"7926527P";"";"http://uk.rs-online.com/web/p/products/7926527P";"";"";
"IC9";"24LC024ST";"24LC024ST";"TSSOP8";"Serial EEPROM";"";"";"";"";"";"";"";"";"";"24LC024H-I/ST";"1659745";"77M3584";"";"";"";"";"";"";
"IC10";"MAX16054AZT+T";"MAX16054AZT+T";"SOT95P275X110-6N";"On Off Controller, Debounce, 15kV ESD MAX16054AZT+T, Voltage Supervisor No Push Button Controller 6-Pin SOT-23";"";"MAX16054AZT+T";"";"http://uk.rs-online.com/web/p/products/9237416";"On Off Controller, Debounce, 15kV ESD MAX16054AZT+T, Voltage Supervisor No Push Button Controller 6-Pin SOT-23";"1.1mm";"Maxim Integrated";"MAX16054AZT+T";"";"";"";"";"";"9237416";"";"http://uk.rs-online.com/web/p/products/9237416";"";"";
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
